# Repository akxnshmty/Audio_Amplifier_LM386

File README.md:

# 🔊 LM386 Audio Amplifier PCB Design

This is a custom-designed audio amplifier circuit using the **LM386** IC, created in **KiCad**. The amplifier is compact, efficient, and suitable for driving small speakers. Ideal for hobbyist audio projects and beginner embedded electronics enthusiasts.

## ⚙️ Features

- ✅ Based on the **LM386** audio amplifier IC.
- 🔋 Powered via a **DC barrel jack** (standard 12V input).
- 🎛️ Integrated **SPST switch** for power control.
- 📉 Includes **bypass capacitor** (C5) for noise reduction.
- 🔊 Potentiometer (RV1) for **volume control**.
- 📦 Designed with **professional component placement and rounded PCB corners**.
- ⚡️ Ground plane with zone fill for better noise immunity.

## 🧩 Components Used

| Component | Description            |
|-----------|------------------------|
| U1        | LM386 Audio Amp IC     |
| RV1       | 10k Potentiometer      |
| SPST      | Power On/Off Switch    |
| C1, C5    | 100µF Electrolytic Caps|
| DC Jack   | Standard Barrel Jack   |
| J1        | Speaker Output Header  |

## 📐 PCB Design Highlights

- Designed in **KiCad** using default libraries.
- Compact layout with minimal track clutter.
- Routed using both front and back layers.
- Rounded board outline for professional aesthetics.
- Track widths and spacing selected for low noise operation.

## 📂 Files Included

- `.kicad_pro` – Project file  
- `.kicad_sch` – Schematic  
- `.kicad_pcb` – PCB layout  

## 🛠️ Getting Started

1. Clone the repository.
2. Open with **KiCad v7 or newer**.
3. Modify the schematic or layout as needed.
4. Export Gerbers and fabricate your PCB!

## 📎 License

MIT License – Free to use and modify.

---

> 🔊 **LM386 Audio Amplifier PCB Design**  
> Designed a minimal yet professional audio amp PCB using the LM386 IC in KiCad.  
> Features a DC barrel jack 🔌, SPST switch 🧷, potentiometer for volume 🎛️, and ground zone fill for improved noise immunity.  
> Rounded corners and clean routing make it look super professional 💼  
> Check it out on linkedin ⬇️  
> 👉 https://www.linkedin.com/in/aakanksh-mohanty-906813193/

Happy PCB Designing😜

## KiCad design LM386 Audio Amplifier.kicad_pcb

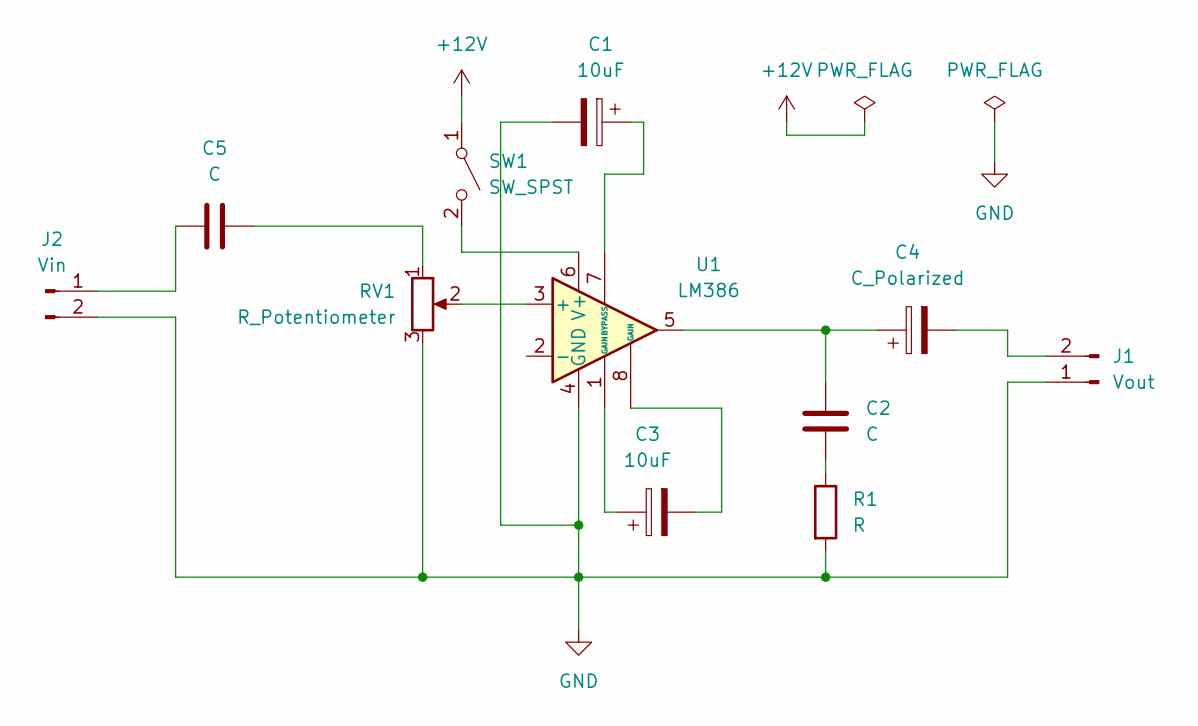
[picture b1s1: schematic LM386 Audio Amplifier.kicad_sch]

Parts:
C1, C3: 10uF; CP_Radial_D5.0mm_P2.00mm
C2, C5: C; C_Disc_D5.0mm_W2.5mm_P2.50mm
C4: C_Polarized; CP_Radial_D5.0mm_P2.00mm
J1: Vout; PinHeader_1x02_P2.54mm_Vertical
J2: Vin; PinHeader_1x02_P2.54mm_Vertical
R1: R; R_Axial_DIN0207_L6.3mm_D2.5mm_P7.62mm_Horizontal
RV1: R_Potentiometer; Potentiometer_Bourns_3296W_Vertical
SW1: SW_SPST; SW_PUSH_6mm
U1: LM386; DIP-8_W7.62mm

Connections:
+12V: SW1.1 (A)
GND: C1.2, J1.1, J2.2, R1.2, RV1.3, U1.4 (GND)
unnamed: C2.1, C4.1, U1.5
unnamed: C2.2, R1.1
unnamed: C3.1, U1.1 (GAIN)
unnamed: C3.2, U1.8 (GAIN)
unnamed: C5.2, RV1.1
unnamed: C4.2, J1.2
unnamed: C5.1, J2.1
unnamed: SW1.2 (B), U1.6 (V+)
unnamed: RV1.2, U1.3 (+)
unnamed: C1.1, U1.7 (BYPASS)

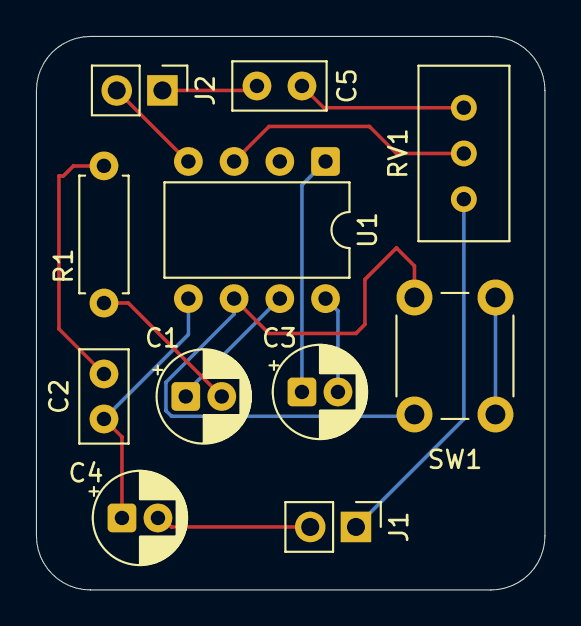
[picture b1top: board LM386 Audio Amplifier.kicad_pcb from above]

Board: 2 copper layers, 28.2 x 30.8 mm, 11 parts (0 on the bottom side), 11 nets.

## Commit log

2025-08-05 README.md
